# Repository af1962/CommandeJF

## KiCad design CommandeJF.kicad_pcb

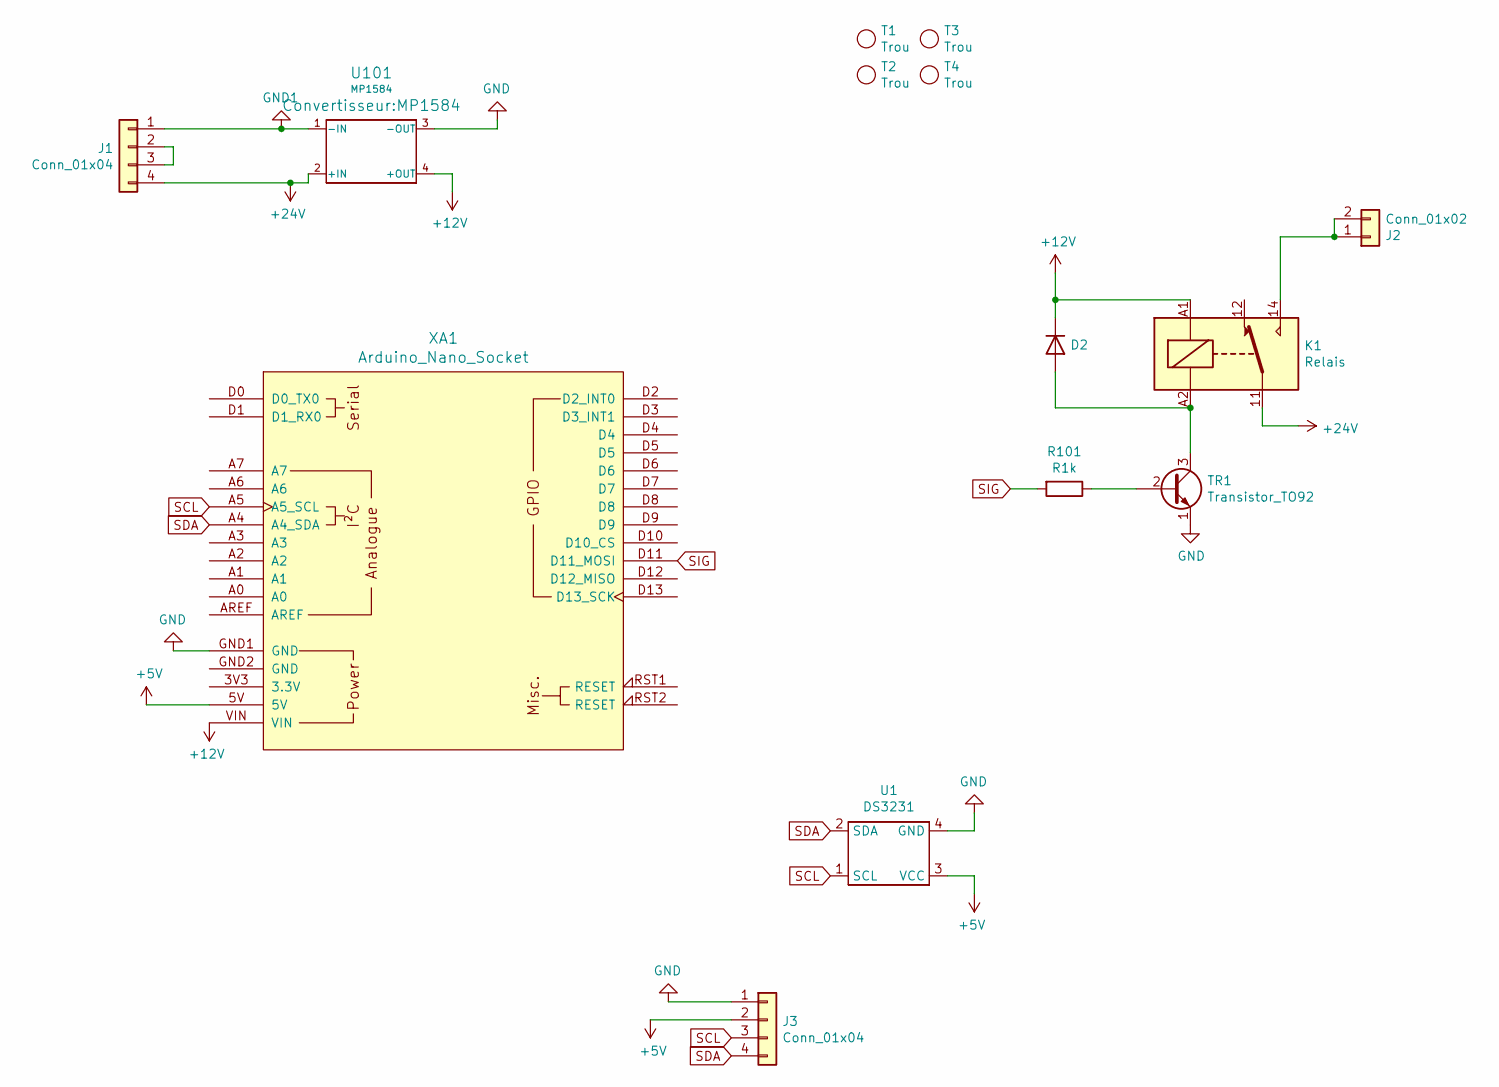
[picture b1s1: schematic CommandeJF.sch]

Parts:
D2: 1N4148; diode_do35
J1: Conn_01x04; TerminalBlock_Phoenix_MKDS-1,5-4-5.08_1x04_P5.08mm_Horizont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
J2: Conn_01x02; TerminalBlock_Phoenix_MKDS-1,5-2-5.08_1x02_P5.08mm_Horizont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
J3: Conn_01x04; JST_XH_B04B-XH-A_04x2.50mm_Straight
K1: Relais; Relais_SRD
R101: R1k; R_025W
T1, T2, T3, T4: Trou; Rond
TR1: Transistor_TO92; TO-92
U1: DS3231; RTC_DS3231
U101: MP1584
XA1: Arduino_Nano_Socket; Arduino_Nano_Module_sur_Socket

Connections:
+5V: J3.2, U1.3 (VCC), XA1.5V
+12V: D2.1 (K), K1.A1, U101.4 (+OUT), XA1.VIN
+24V: J1.4, K1.11, U101.2 (+IN)
GND: J3.1, TR1.1 (E), U1.4 (GND), U101.3 (-OUT), XA1.GND1 (GND)
GND1: J1.1, U101.1 (-IN)
unnamed: D2.2 (A), K1.A2, TR1.3 (C)
unnamed: J1.2, J1.3
unnamed: J2.1, J2.2, K1.14
unnamed: R101.1, TR1.2 (B)
SCL: J3.3, U1.1 (SCL), XA1.A5 (A5_SCL)
SDA: J3.4, U1.2 (SDA), XA1.A4 (A4_SDA)
SIG: R101.2, XA1.D11 (D11_MOSI)

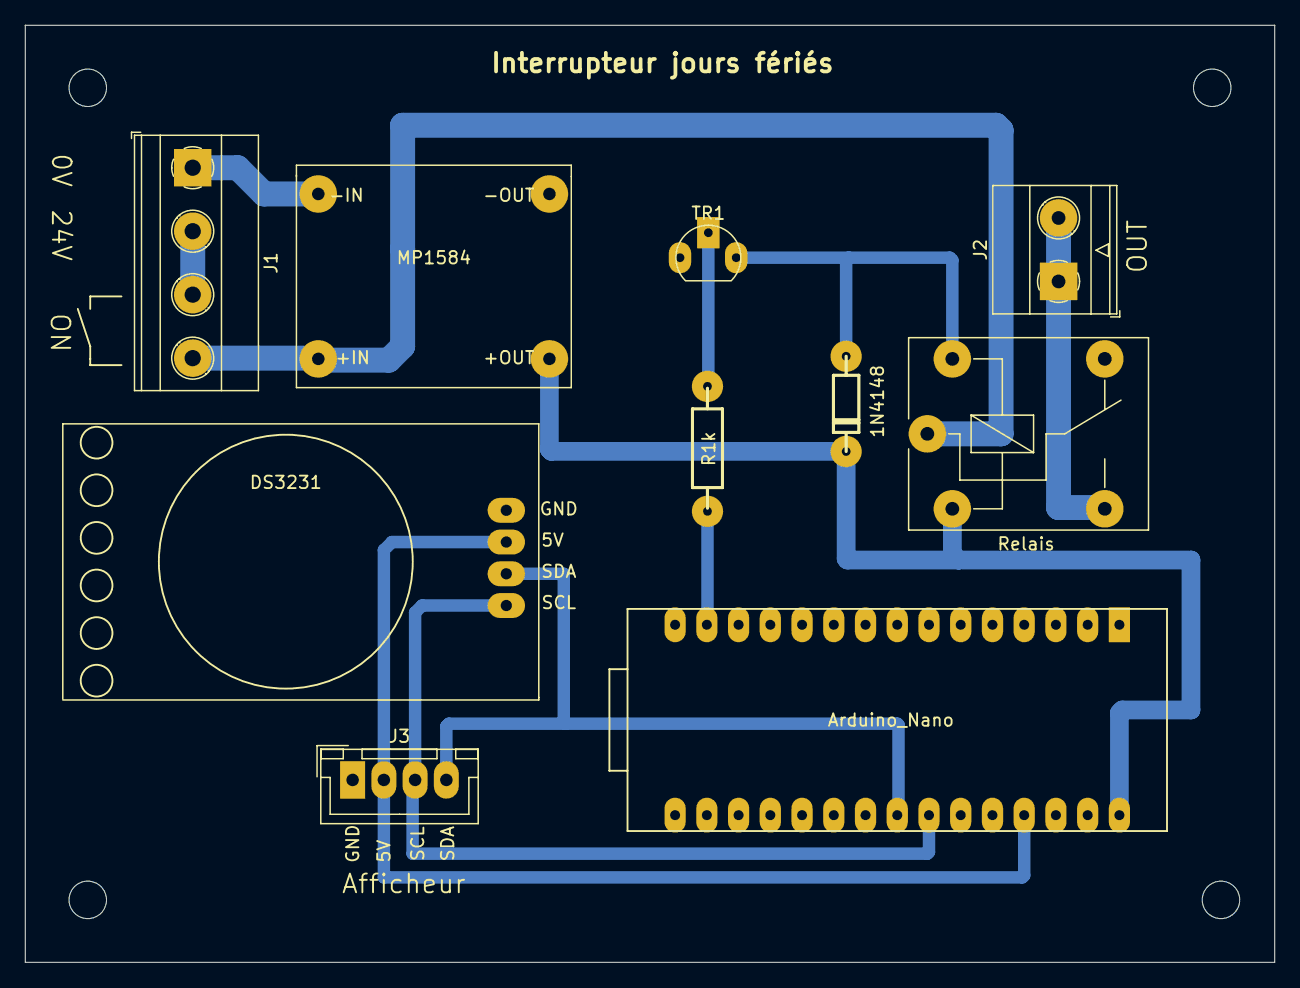
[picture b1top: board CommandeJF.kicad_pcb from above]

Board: 2 copper layers, 100.0 x 75.0 mm, 14 parts (0 on the bottom side), 12 nets.

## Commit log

2022-05-11 Ajouter .gitattributes et .gitignore
2022-05-11 Ajoutez des fichiers projet.
2023-03-30 Original
2023-03-31 Mise en forme
2023-04-02 Arduino nano
2023-04-06 version 1
2023-04-09 Version finale
